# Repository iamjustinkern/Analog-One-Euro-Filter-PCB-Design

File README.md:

# Analog-One-Euro-Filter-PCB-Design
The circuit schematic models a Velocity Tracking - Voltage Controlled Filter. Essentially, it is an analog implementation of an One-Euro Filter.
This circuit solves the issue of noise you get when you slowly turn a knob from a low-pass soothing filter. As well as this, it will adaptively give you zero delay when you do change the parameters quickly as a heavy soothing filter typically involves some lag. Outside of the control signal soothing, it has this same effect with an input audio signal. For more sustained soft notes, the filter bandwidth would remain smaller and suppress any background hissing noise. For sharp transient attacks, the filter bandwidth will adaptively expand to maintain the characteristic of a bright sharp sound. 

Included in the repo are the KiCad files needed to print your own version of this circuit. As well as LTspice simulations as a proof of concept.

There are four major stages in this schematic that make up the architecture. 
  1. Differentiator Stage
  2. Full Wave Rectifier
  3. Alpha Control and Filter Staging
  4. LT1228 Low Pass Filtering

Differentiator Stage:

This circuit calculates the time derivative of the input signal. This is important for capturing the velocity of the input signal. In audio this corresponds with the rate of change in voltage for that signal.
The main components of this circuit involve a AD713 Operational Amplifier, with a negative feedback loop. The feedback loop has a 47K resistor coupled with a 100nF capacitor in parallel with it. From the input signal it goes through a 1K resistor and 1uF capacitor. The capacitor in the feedback loop helps give a roll off to the signal and the resistors help protect against high frequency stability issues.

Full Wave Rectifier Stage:

The Full-Wave Rectifier Circuit above converts the V_vel signal into its absolute value form. Now none of the Sine waves will be below 0. Operation Amplifiers U3 and U4 serve as a way to make the “imperfect” use of the diodes more effective with its negative feedback loops. It allows for greater precision at smaller voltage levels.

The diodes themselves help serve the rectification functionality. Putting the diodes in the op-amp loop erases their normal 0.7 volt turn on requirement. Diode 2 turns on during the positive volt swings of the sine wave. It helps route the signal for the full-wave math. Diode 1 turns on when negative swings in the signal to keep the op-amp from locking up and making the switch in directions instantaneous.

The R7 resistor has a ratio of 2:1 with the R9 resistor. It gives the half-wave path double the weight than the direct one. All the other resistors help keep the signal sizes consistent and equal.

Alpha Control and Filter Staging:

At this part of this stage of the system, we integrate a way to tune the system and execute the 1-Euro math in hardware (Fc = Fc_min + Vvel). The circuit outputs a fixed DC voltage coming from V8. This exact voltage can be tuned by R11. This resistor can change the cutoff frequency that is used to sooth the signal. During high speed motion this circuit eliminates the lag involved. The rectified signal goes through R10, which is used to tune the sensitivity of how the circuit reacts to fast movement. The voltage coming from R10 is added with the baseline voltage which boosts the signal. This forces the filter's bandwidth to open wider and lets fast movements pass through without delay. 

Op-amp U5, is what drives that summing and scaling that I mentioned above.

And op-amp U6, helps invert the signal back to its original state since the last op-amp U5 inverted it originally. It also makes sure that signal remains strong before it goes into LT1228

LT1228 Low Pass Filtering:

At the LT1228 chip is where the adaptive filtering takes place. Inside the chip contains two different amplifiers. A variable current amp and an output buffer. 

The signal flow for the variable current amp is as follows. The V_control signal coming from the filter staging circuit is fed into the Iset pin. When V_control is high it pushes high current through and when it is low, it pushes very low current. This is supposed to support the adaptive filtering mechanism of the system. The current comes out of Iout at pin 1. From there it charges the capacitor C1. If it is high current, then there is no delay and passes the high frequency content. When the current is low, the capacitor charges more slowly which allows for the signal to be smooth out and rid of the high frequency noise.

We have the output buffer stage because we don’t want to mess up the capacitor when trying to get the output. So, the second amplifier reads the voltage from the capacitor and copies it to Vout to not drain the capacitor of any power.

Finally, In- creates a global feedback loop that keeps the whole system stable and ensures that the output matches the original input.

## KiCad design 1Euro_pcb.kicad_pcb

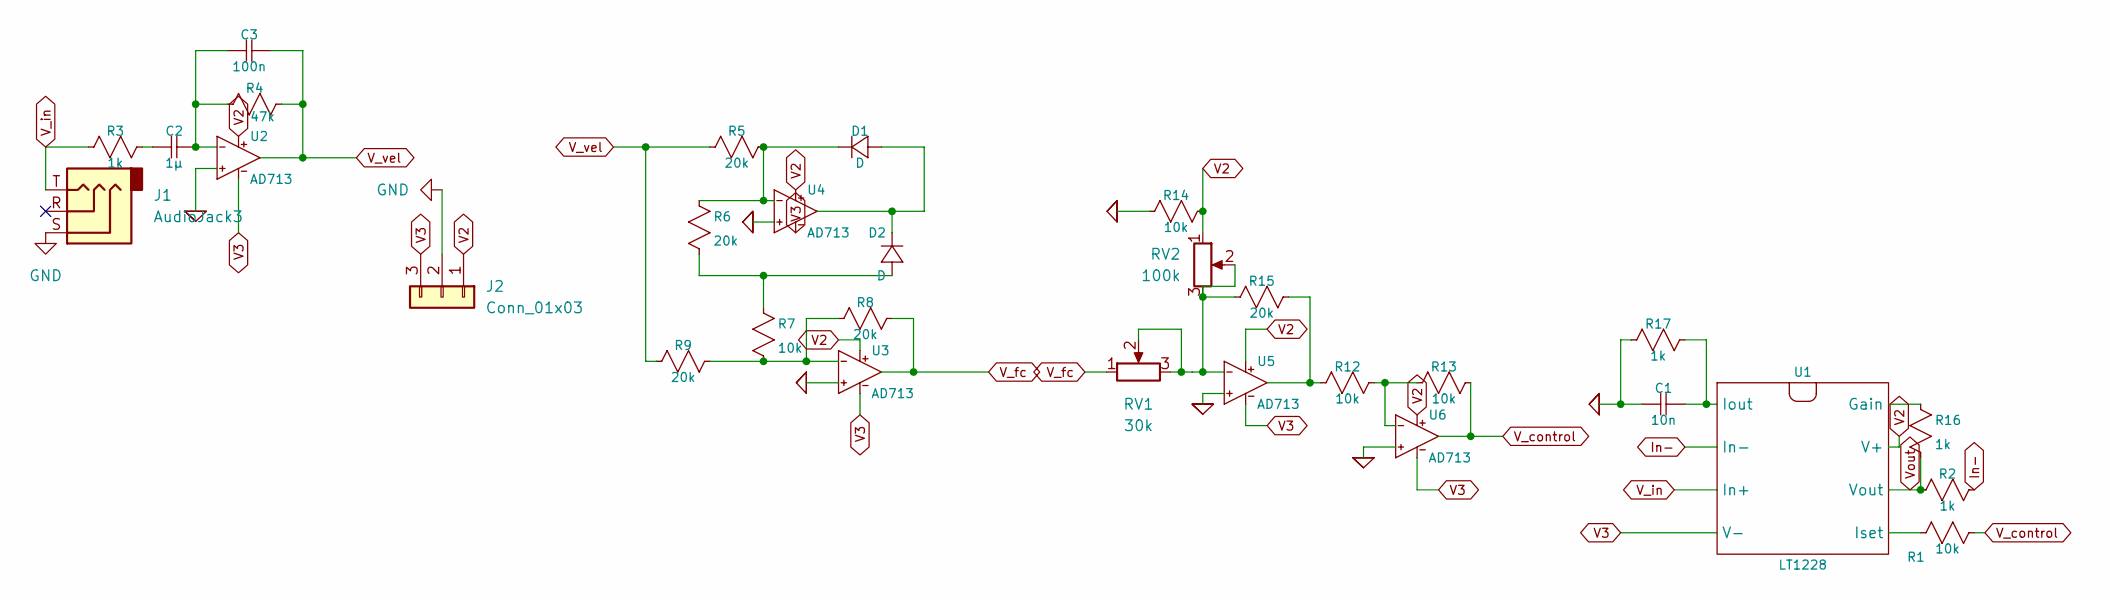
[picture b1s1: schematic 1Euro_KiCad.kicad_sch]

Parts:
C1: 10n; C_1206_3216Metric_Pad1.33x1.80mm_HandSolder
C2: 1µ; C_1206_3216Metric_Pad1.33x1.80mm_HandSolder
C3: 100n; C_1206_3216Metric_Pad1.33x1.80mm_HandSolder
D1, D2: D; D_SOD-123
J1: AudioJack3; Jack_3.5mm_CUI_SJ-3523-SMT_Horizontal
J2: Conn_01x03; PinHeader_1x03_P2.54mm_Vertical
R1, R7, R12, R13, R14: 10k; R_1206_3216Metric_Pad1.30x1.75mm_HandSolder
R2, R3, R16, R17: 1k; R_1206_3216Metric_Pad1.30x1.75mm_HandSolder
R4: 47k; R_1206_3216Metric_Pad1.30x1.75mm_HandSolder
R5, R6, R8, R9, R15: 20k; R_1206_3216Metric_Pad1.30x1.75mm_HandSolder
RV1: 30k; Potentiometer_Bourns_3296W_Vertical
RV2: 100k; Potentiometer_Bourns_3296W_Vertical
U1: LT1228; SO-8_S_LIT
U2, U3, U4, U5, U6: AD713; RJ_5_ADI

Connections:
0: C1.2, R14.1, R17.2, U2.1 (In+), U3.1 (In+), U4.1 (In+), U5.1 (In+), U6.1 (In+)
GND: J1.S, J2.2
In-: R2.1, U1.2 (In-)
unnamed: C2.2, R3.1
unnamed: D1.1 (+), D2.2 (-), U4.5 (OUT)
unnamed: D1.2 (-), R5.1, R6.1, U4.2 (In-)
unnamed: D2.1 (+), R6.2, R7.1
unnamed: R16.1, U1.8 (Gain)
unnamed: C1.1, R17.1, U1.1 (Iout)
unnamed: R1.2, U1.5 (Iset)
unnamed: C2.1, C3.2, R4.2, U2.2 (In-)
unnamed: R7.2, R8.2, R9.1, U3.2 (In-)
unnamed: R15.2, RV1.2, RV1.3, RV2.2, RV2.3, U5.2 (In-)
unnamed: R12.2, R15.1, U5.5 (OUT)
unnamed: R12.1, R13.2, U6.2 (In-)
V2: J2.1, R14.2, RV2.1, U1.7 (V+), U2.3 (V+), U3.3 (V+), U4.3 (V+), U5.3 (V+), U6.3 (V+)
V3: J2.3, U1.4 (V-), U2.4 (V-), U3.4 (V-), U4.4 (V-), U5.4 (V-), U6.4 (V-)
V_control: R1.1, R13.1, U6.5 (OUT)
V_fc: R8.1, RV1.1, U3.5 (OUT)
V_in: J1.T, R3.2, U1.3 (In+)
V_vel: C3.1, R4.1, R5.2, R9.2, U2.5 (OUT)
Vout: R2.2, R16.2, U1.6 (Vout)

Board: 2 copper layers, 30 parts (0 on the bottom side), 22 nets, no tracks yet.
